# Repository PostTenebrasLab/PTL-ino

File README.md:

# PTL-ino

The PTL-ino (“petilino”) is a *uino-compatbile board that is fully made of easily solderable through-hole components.

You can find more general information at http://ptl-ino.com

The current Kicad file were made with Kicad 4.0.2, so please upgrade to Kicad 4 if you haven't already.
The Gerber file are there in case you simply want to order PCB directly to service like OSHPark or DirtyPCB.

If you plan to sell board based on this design, you have to remove our logo from the PCB.

PTL-ino board is licensed with Creative Common BY-SA 4.0 (https://creativecommons.org/licenses/by-sa/4.0/)

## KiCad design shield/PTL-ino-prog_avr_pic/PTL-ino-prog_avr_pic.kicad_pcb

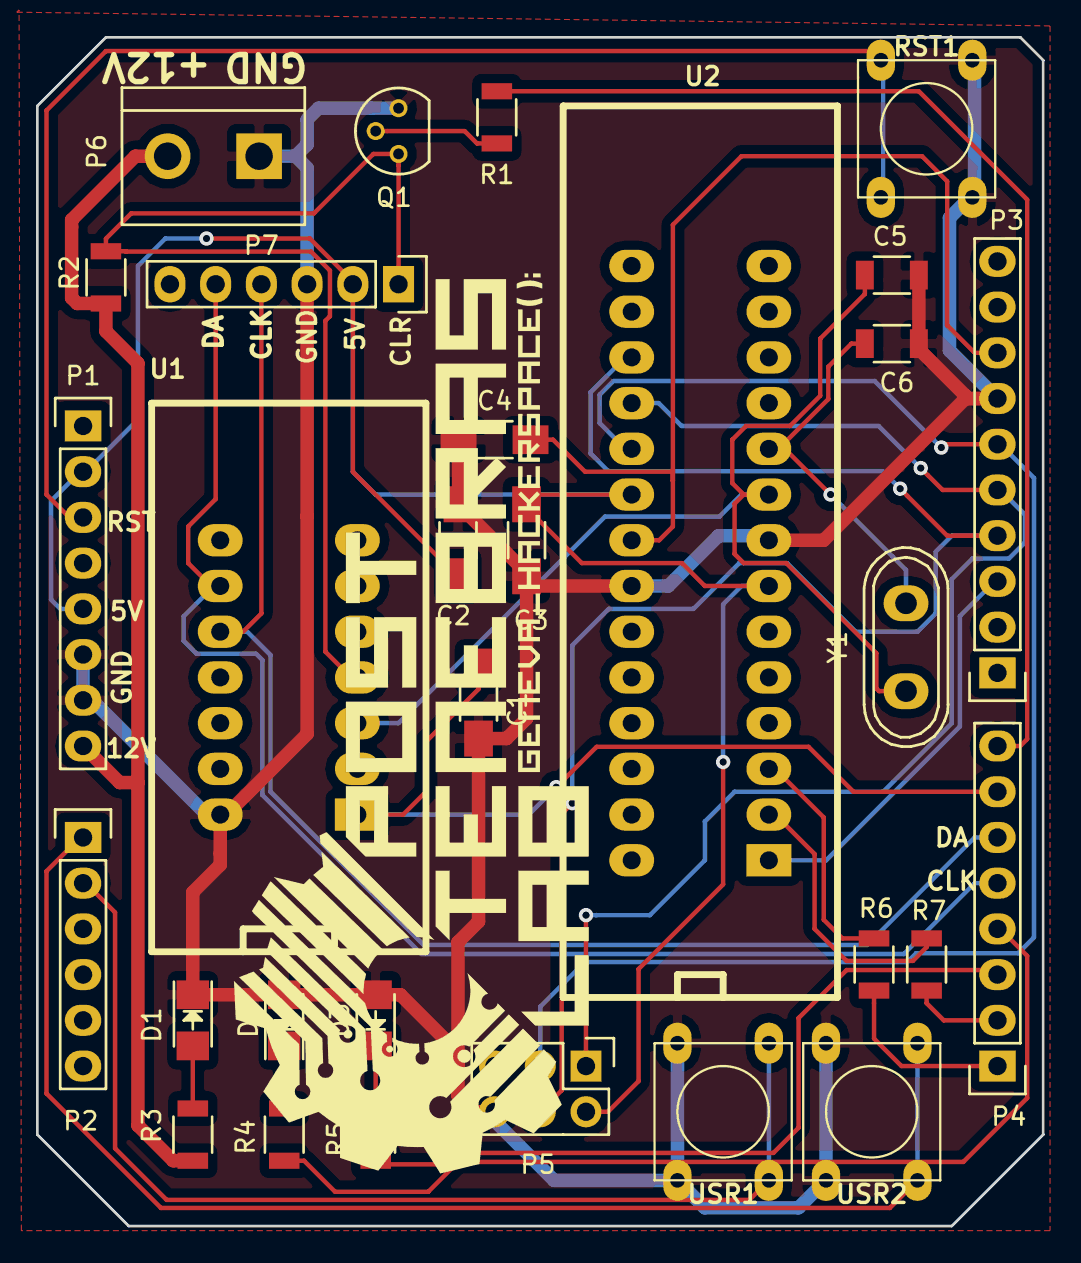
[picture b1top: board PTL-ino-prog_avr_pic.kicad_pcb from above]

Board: 2 copper layers, 55.9 x 66.0 mm, 30 parts (0 on the bottom side), 28 nets.

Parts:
C1: 220n; C_1206_HandSoldering
C2, C3, C4: 100n; C_1206_HandSoldering
C5, C6: 20pF; C_1206
D1: LED1; LED_1206
D2: LED2; LED_1206
D3: LED3; LED_1206
P1, P4: CONN_8; Pin_Header_Straight_1x08
P2, P7: CONN_6; Pin_Header_Straight_1x06
P3: CONN_10; Pin_Header_Straight_1x10
P5: CONN_3X2; Pin_Header_Straight_2x03
P6: CONN_01X02; bornier2
Q1: BC548; TO-92_Molded_Narrow
R1: 4K7; R_1206
R2: 10K; R_1206
R3: 1K; R_1206
R4, R5: 220; R_1206
R6, R7: R220; R_1206
RST1: RST; SW_PUSH_SMALL
U1: PIC16F1455; ZIF-14
U2: ATmega328; ZIF-28
USR1, USR2: SW_PUSH; SW_PUSH_SMALL
Y1: Crystal; Crystal_HC50-U_Vertical

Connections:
+5V: C2.1, C3.1, P1.2, P1.5, P5.2, P7.2, U2.7, U2.20
+12V: P1.8, P6.2, R2.1, R3.1
/0: P4.1, R6.1
/1: P4.2, R7.2
/2: P4.3, R5.2
/3: P4.4, R4.2
/4: P4.5, P7.5, U1.9
/5: P4.6, P7.4, U1.10
/6: C1.2, P4.7, U1.1
/7: P4.8, R1.2
/10: P3.3, U2.1
/11: P3.4, P5.4, U2.17
/12: P3.5, P5.1, U2.18
/13: P3.6, P5.3, U2.19
/14: P2.1, USR2.1
/15: P2.2, USR1.1
/AREF: C4.1, P3.8, U2.21
/~MCLR: P7.1, Q1.1, R2.2, U1.4
/~RST: P1.3, RST1.1
GND: C1.1, C2.2, C3.2, C4.2, C5.1, C6.2, D1.1, D2.2, D3.2, P1.6, P1.7, P3.7, P5.6, P6.1, P7.3, Q1.3, RST1.2, U1.14, U2.8, U2.22, USR1.2, USR2.2
unnamed: C5.2, U2.9, Y1.1
unnamed: C6.1, U2.10, Y1.2
unnamed: D1.2, R3.2
unnamed: D2.1, R4.1
unnamed: D3.1, R5.1
unnamed: Q1.2, R1.1
unnamed: R6.2, U2.3
unnamed: R7.1, U2.2

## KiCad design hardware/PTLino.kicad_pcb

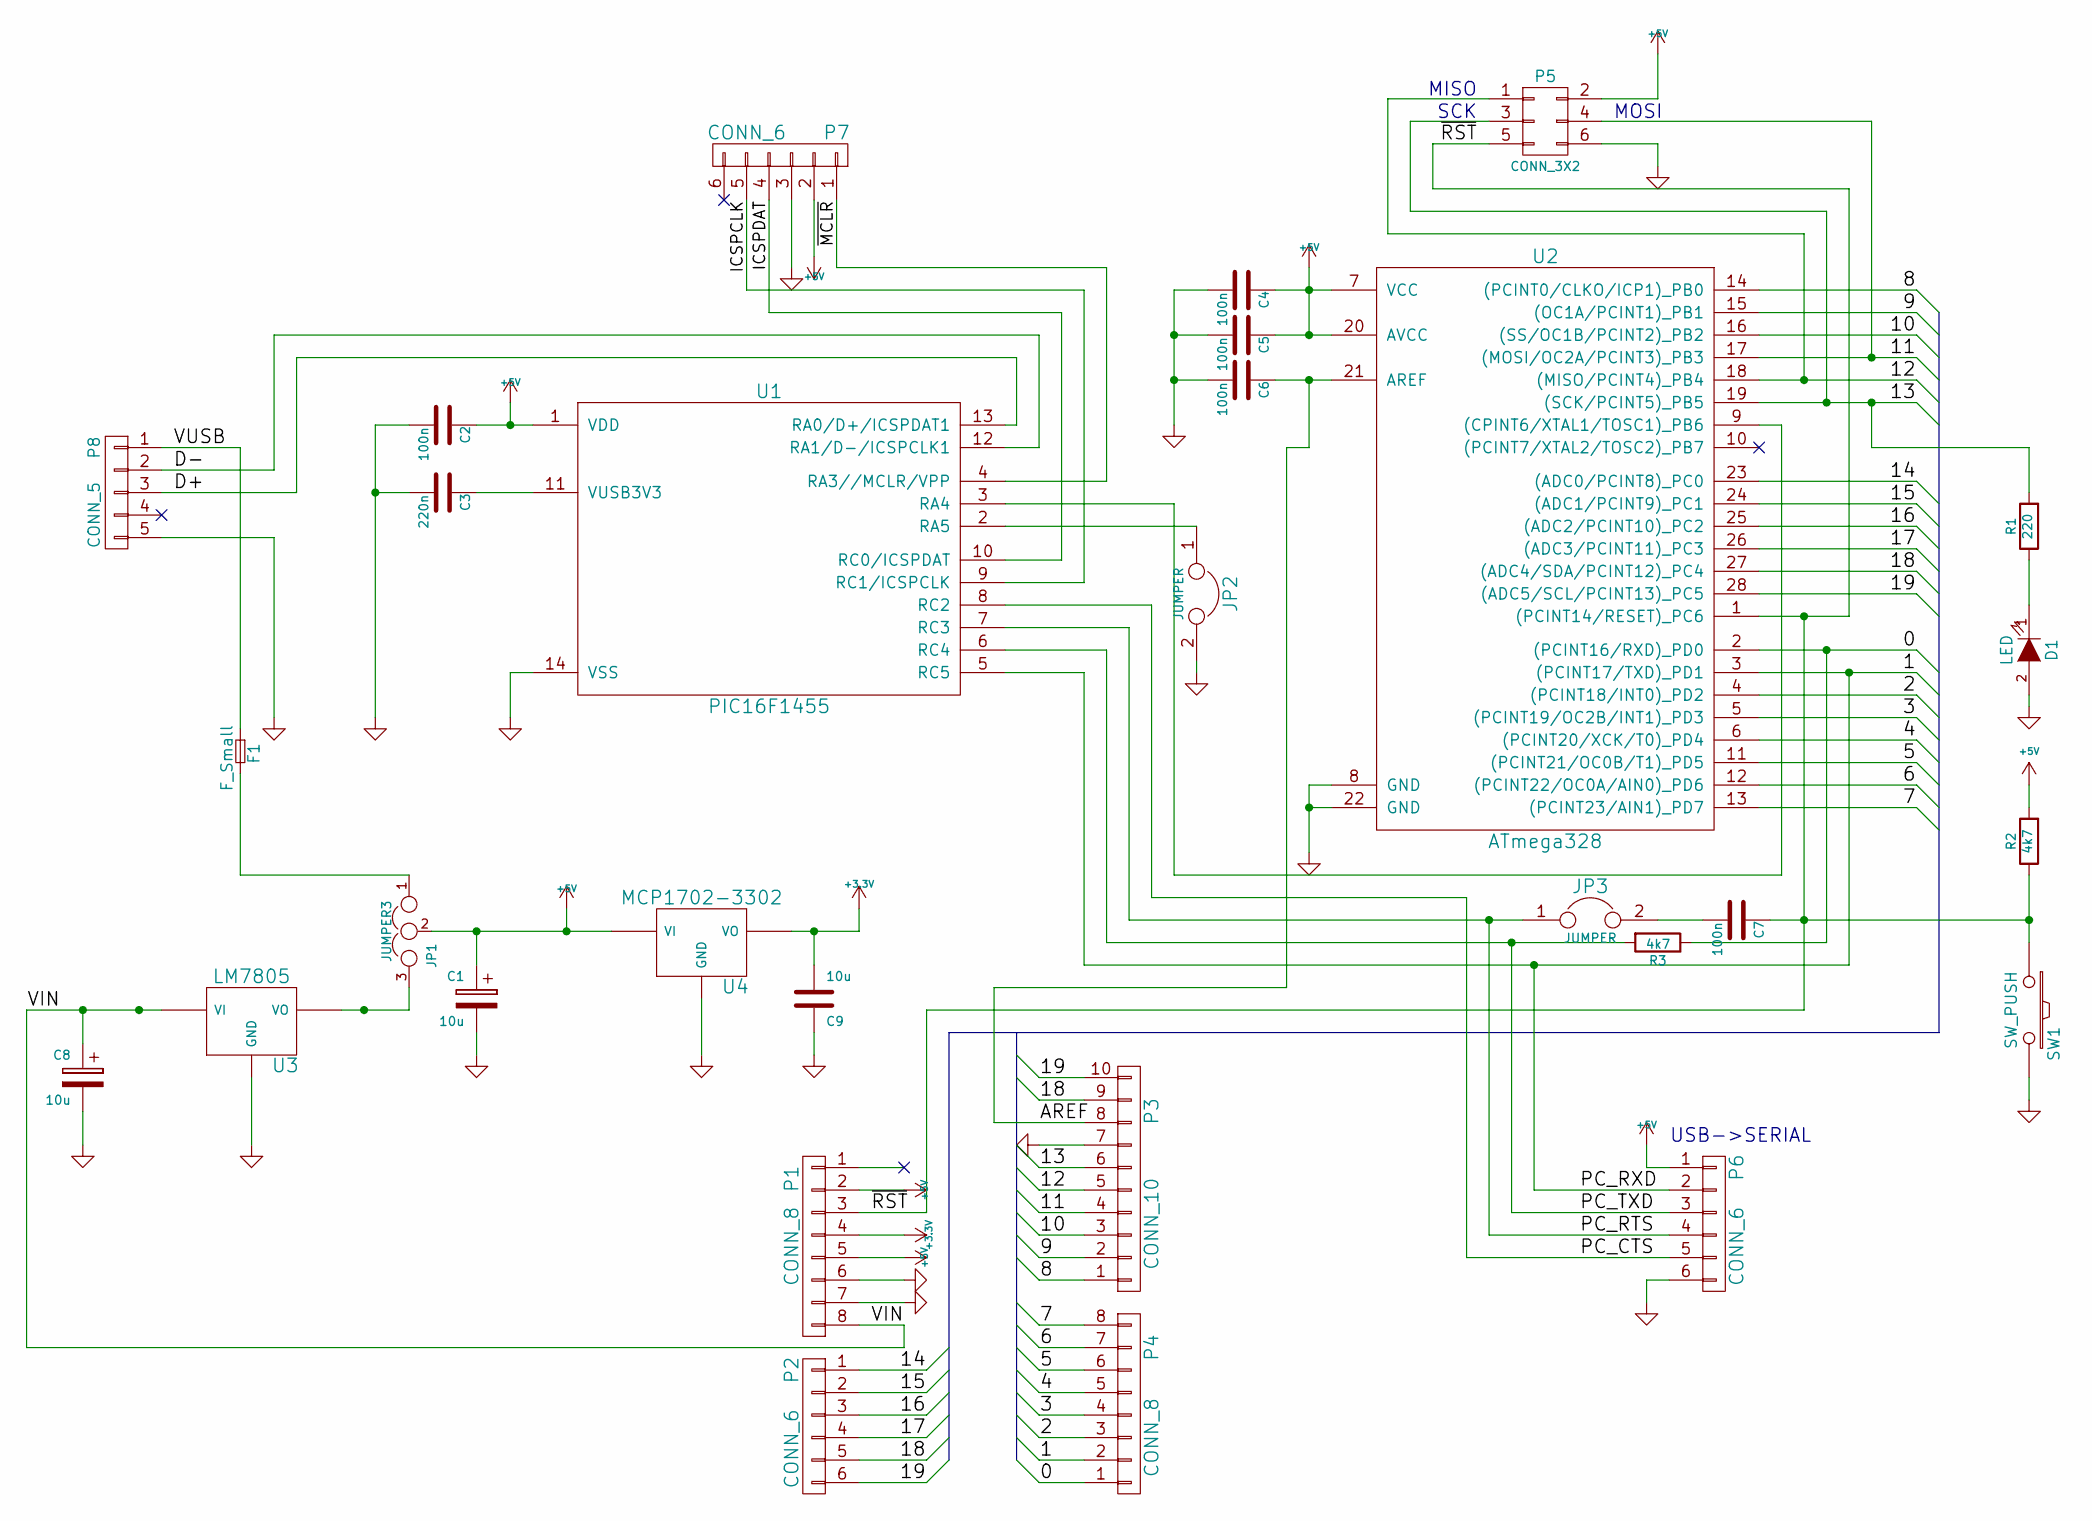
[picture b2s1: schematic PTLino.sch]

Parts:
C1, C8: 10u; C1V7H
C2, C4, C5, C6, C7: 100n; C1
C3: 220n; C1
C9: 10u; C1_pol
D1: LED; LEDV
F1: F_Small; F1
JP1: JUMPER3; solder-jumper-3
JP2, JP3: JUMPER; solder-jumper-2
P1, P4: CONN_8; SIL-8
P2, P6, P7: CONN_6; SIL-6
P3: CONN_10; SIL-10
P5: CONN_3X2; pin_array_3x2
P8: CONN_5; USB-mini-TH
R1: 220; R3-5
R2, R3: 4k7; R3-5
SW1: SW_PUSH; SW_PUSH_SMALL
U1: PIC16F1455; DIP-14__300_ELL
U2: ATmega328; DIP-28__300_ELL
U3: LM7805; TO220
U4: MCP1702-3302; TO92

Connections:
+3V3: C9.2, P1.4, U4.1 (VO)
+5V: C1.1, C2.1, C4.1, C5.1, JP1.2, P1.2, P1.5, P5.2, P6.1, P7.2, R2.2, U1.1 (VDD), U2.7 (VCC), U2.20 (AVCC), U4.2 (VI)
/0: P4.1, R3.1, U2.2 ((PCINT16/RXD)_PD0)
/1: P4.2, P6.2, U1.5 (RC5), U2.3 ((PCINT17/TXD)_PD1)
/2: P4.3, U2.4 ((PCINT18/INT0)_PD2)
/3: P4.4, U2.5 ((PCINT19/OC2B/INT1)_PD3)
/4: P4.5, U2.6 ((PCINT20/XCK/T0)_PD4)
/5: P4.6, U2.11 ((PCINT21/OC0B/T1)_PD5)
/6: P4.7, U2.12 ((PCINT22/OC0A/AIN0)_PD6)
/7: P4.8, U2.13 ((PCINT23/AIN1)_PD7)
/8: P3.1, U2.14 ((PCINT0/CLKO/ICP1)_PB0)
/9: P3.2, U2.15 ((OC1A/PCINT1)_PB1)
/10: P3.3, U2.16 ((SS/OC1B/PCINT2)_PB2)
/11: P3.4, P5.4, U2.17 ((MOSI/OC2A/PCINT3)_PB3)
/12: P3.5, P5.1, U2.18 ((MISO/PCINT4)_PB4)
/13: P3.6, P5.3, R1.2, U2.19 ((SCK/PCINT5)_PB5)
/14: P2.1, U2.23 ((ADC0/PCINT8)_PC0)
/15: P2.2, U2.24 ((ADC1/PCINT9)_PC1)
/16: P2.3, U2.25 ((ADC2/PCINT10)_PC2)
/17: P2.4, U2.26 ((ADC3/PCINT11)_PC3)
/18: P2.5, P3.9, U2.27 ((ADC4/SDA/PCINT12)_PC4)
/19: P2.6, P3.10, U2.28 ((ADC5/SCL/PCINT13)_PC5)
/AREF: C6.1, P3.8, U2.21 (AREF)
/D+: P8.3, U1.13 (RA0/D+/ICSPDAT1)
/D-: P8.2, U1.12 (RA1/D-/ICSPCLK1)
/ICSPCLK: P7.5, U1.9 (RC1/ICSPCLK)
/ICSPDAT: P7.4, U1.10 (RC0/ICSPDAT)
/PC_CTS: P6.5, U1.8 (RC2)
/PC_RTS: JP3.1, P6.4, U1.7 (RC3)
/PC_TXD: P6.3, R3.2, U1.6 (RC4)
/VIN: C8.1, P1.8, U3.2 (VI)
/VUSB: F1.1, P8.1
/~MCLR: P7.1, U1.4 (RA3//MCLR/VPP)
/~RST: C7.1, P1.3, P5.5, R2.1, SW1.1, U2.1 ((PCINT14/RESET)_PC6)
GND: C1.2, C2.2, C3.2, C4.2, C5.2, C6.2, C8.2, C9.1, D1.2 (A), JP2.2, P1.6, P1.7, P3.7, P5.6, P6.6, P7.3, P8.5, SW1.2, U1.14 (VSS), U2.8 (GND), U2.22 (GND), U3.3 (GND), U4.3 (GND)
unnamed: C3.1, U1.11 (VUSB3V3)
unnamed: C7.2, JP3.2
unnamed: D1.1 (K), R1.1
unnamed: F1.2, JP1.1
unnamed: JP1.3, U3.1 (VO)
unnamed: JP2.1, U1.2 (RA5)
unnamed: U1.3 (RA4), U2.9 ((CPINT6/XTAL1/TOSC1)_PB6)

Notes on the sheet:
MOSI
MISO
SCK
USB->SERIAL

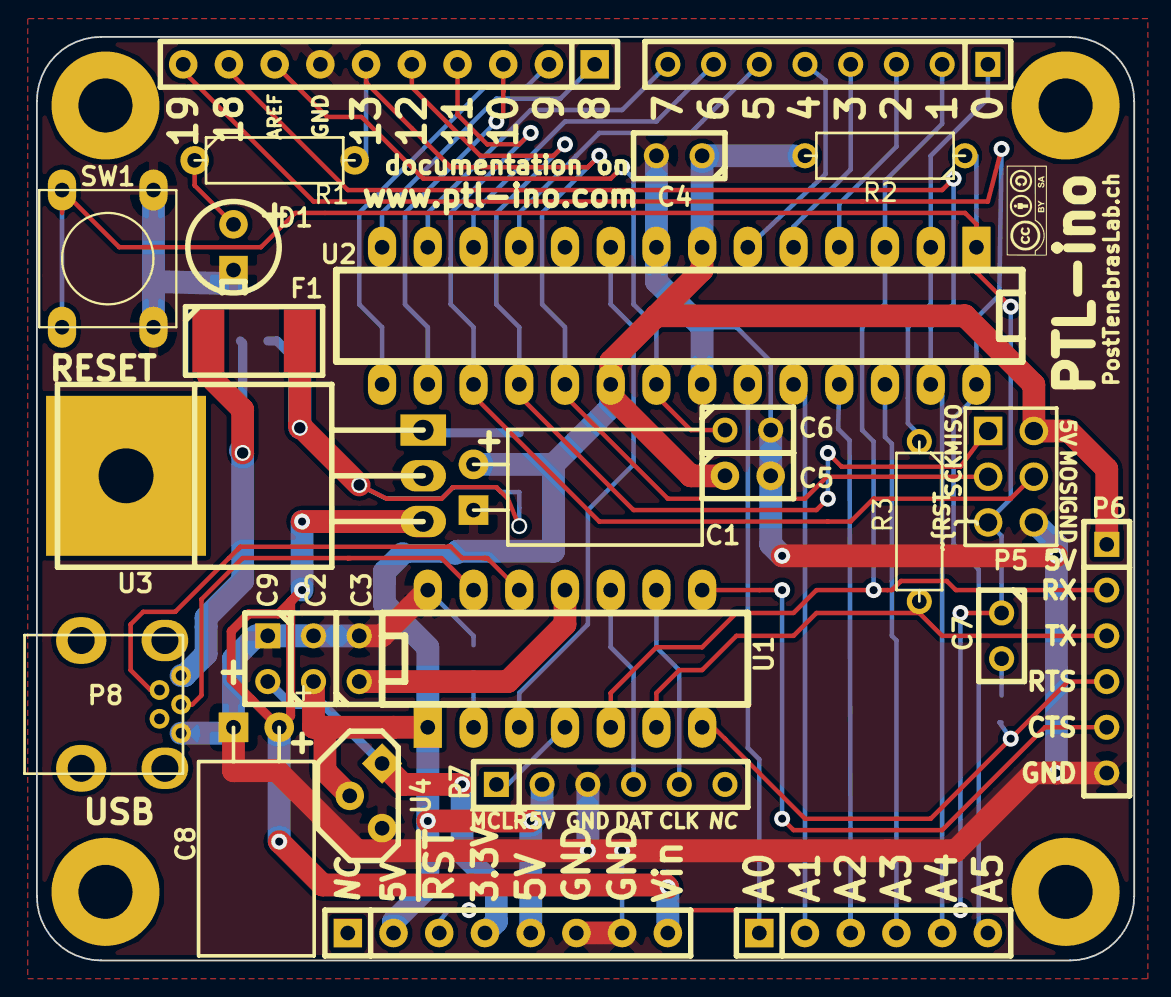
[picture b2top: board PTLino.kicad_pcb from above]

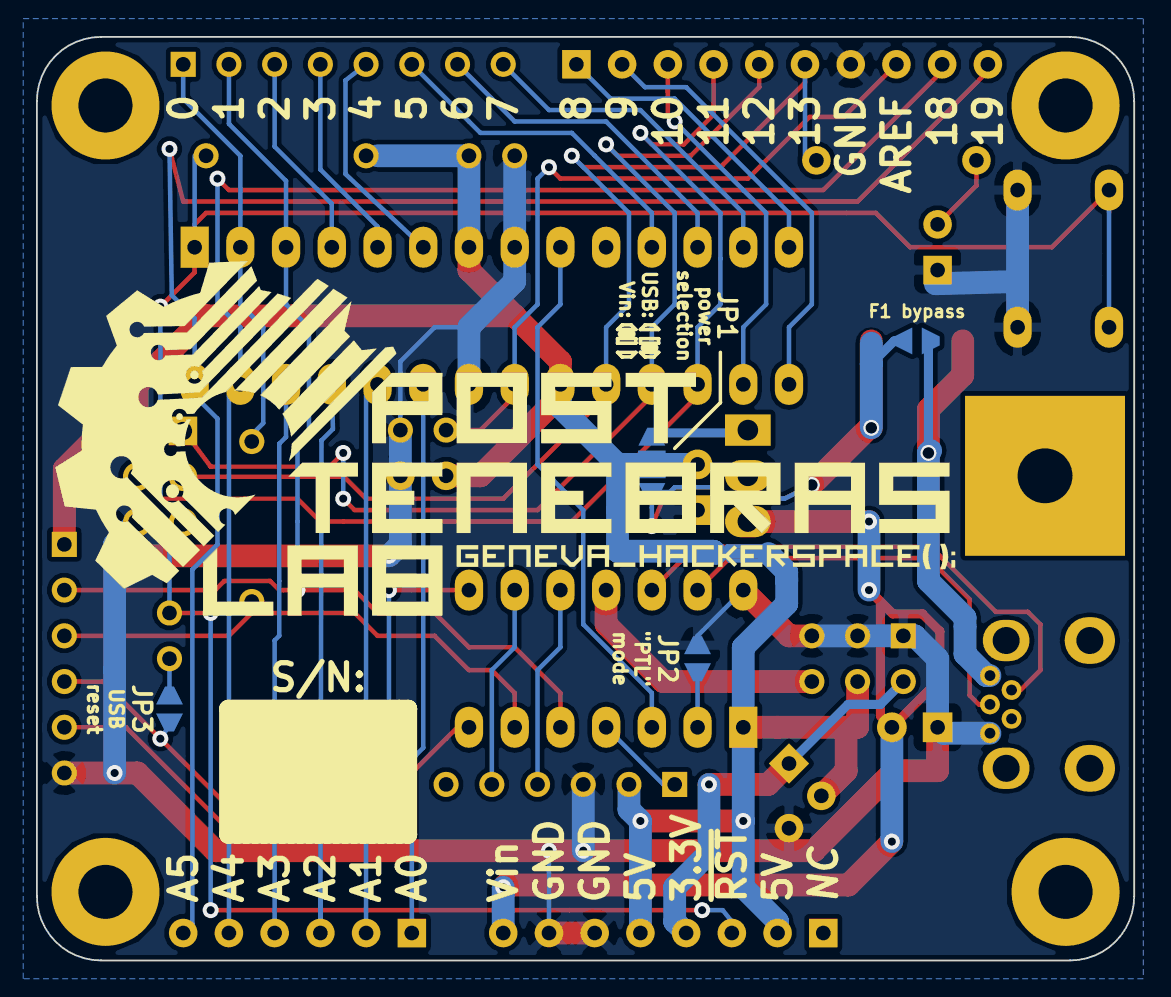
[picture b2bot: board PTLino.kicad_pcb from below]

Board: 2 copper layers, 61.0 x 51.3 mm, 35 parts (3 on the bottom side), 42 nets.

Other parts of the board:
CCBYSA: LOGO; Logo_silk_CC-BY-SA_5x2mm
mouting hole 3mm, mouting hole 3mm#2, mouting hole 3mm#3, mouting hole 3mm#4: VAL**; mounting-hole-3mm

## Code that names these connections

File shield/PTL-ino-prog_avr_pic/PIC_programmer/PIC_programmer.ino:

#define ICSPCLK 4
#define ICSPDAT 5
#define PICVDD  6
#define MCLR    7


#define CONFIG_WORD_1 0x0FA4
#define CONFIG_WORD_2 0x1FEF
#define WORD1_ADDR 7
#define WORD2_ADDR 7

enum pic_cmd {
  LOAD_CONF = 0,
  LOAD_FOR_PROG_MEM = 2,
  READ_FOR_PROG_MEM = 4,
  INC_ADDR = 6,
  RST_ADDR = 0x16,
  BEG_INTERNAL_TIMED_PROG = 0x8,
  BEG_EXTERNAL_TIMED_PROG = 0x18,
  BULK_ERASE_PROG_MEM = 0x9,
  ROW_ERASE_PROG_MEM = 0x11
};




/* Set vpp_entry_mode (programming mode)
 * 
 */
void vpp_entry_mode(){
  digitalWrite(ICSPCLK, LOW);
  digitalWrite(ICSPDAT, LOW);
  
  digitalWrite(MCLR, HIGH);
  delay(1);
  digitalWrite(PICVDD, HIGH);
  delay(1);
  
}

/* Write two word in config
 * 
 */
void set_pic_config(){

  // reset to 0x8000
  pic_cmd_call_wdata(LOAD_CONF, CONFIG_WORD_1);

  // jump to 0x8007
  for(int i = 0; i < WORD1_ADDR; i++)
    pic_cmd_call(INC_ADDR);

  pic_cmd_call(BEG_INTERNAL_TIMED_PROG);

  delayMicroseconds(2);
  
  // reset to 0x8000
  pic_cmd_call_wdata(LOAD_CONF, CONFIG_WORD_1);

  // jump to 0x8007
  for(int i = 0; i < WORD2_ADDR; i++)
    pic_cmd_call(INC_ADDR);

  pic_cmd_call(BEG_INTERNAL_TIMED_PROG);

  delayMicroseconds(2);

}

/* Write data from PIC's address 0x0000
 * 
 */
void write_data(short data_len, short * data){

  // Reset to address 0x000
  pic_cmd_call(RST_ADDR);

  // ERASE MEM
  pic_cmd_call(BULK_ERASE_PROG_MEM);
  // Max erase time 5ms
  delay(6);
  
  for(int i = 0; i < data_len; i++){

    // one word (16 bit word 0-14bit-0)
    for(int j = 0; j < 16; j++){
      digitalWrite(ICSPCLK, HIGH);
      digitalWrite(ICSPDAT, (((*data) >> j) & 1));
      digitalWrite(ICSPCLK, LOW);
    }
    
    data++;
    delayMicroseconds(2);
    pic_cmd_call(INC_ADDR);
    delayMicroseconds(2);
  }
}


/* Send cmd to pic with data as paylod (14 first bit significant)
 *  
 */
void pic_cmd_call_wdata(pic_cmd cmd, short data){

  //load configuration command
  digitalWrite(ICSPDAT, LOW);

  for( int i = 0; i < 6; i++){
    digitalWrite(ICSPCLK, HIGH);
    digitalWrite(ICSPDAT, ((cmd >> i) & 1));
    digitalWrite(ICSPCLK, LOW);
  }
  delayMicroseconds(2);  // one is enought

  // one word (14 bit word)
  for(int i = 0; i < 16; i++){
    digitalWrite(ICSPCLK, HIGH);
    digitalWrite(ICSPDAT, ((data >> i) & 1));
    digitalWrite(ICSPCLK, LOW);
  }
  
}

/* Send cmd to pic 
 *  
 */
void pic_cmd_call(pic_cmd cmd){

  //load configuration command
  digitalWrite(ICSPDAT, LOW);

  for( int i = 0; i < 6; i++){
    digitalWrite(ICSPCLK, HIGH);
    digitalWrite(ICSPDAT, ((cmd >> i) & 1));
    digitalWrite(ICSPCLK, LOW);
  }
  delayMicroseconds(2);  // one is enought
}


void setup() {
  // put your setup code here, to run once:

  pinMode(ICSPCLK, OUTPUT);
  pinMode(ICSPDAT, OUTPUT);
  pinMode(PICVDD, OUTPUT);
  pinMode(MCLR, OUTPUT);

  digitalWrite(ICSPCLK, LOW);
  digitalWrite(ICSPDAT, LOW);
  digitalWrite(PICVDD, LOW);
  digitalWrite(MCLR, LOW);

  // put in Vpp mode
  vpp_entry_mode();
  
  // set config
  set_pic_config();

  
}

void loop() {
  // put your main code here, to run repeatedly:

}

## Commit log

2015-11-14 Update README.md
    Initial simple readme with link to ptl-ino.com
2015-11-14 Created initial structure: Hardware and Software folders. Contain a .gitignore file as a workaround to empty dir.
2015-11-14 Added our doc on how to build the ptl-ino kit (FR + EN) This is a conversion of current doc to ASCIIDOC format. ptl.dozuki.com/Guide/How+to+build+a+PTL-ino+board/
2015-11-14 Corrected typo
2015-11-14 Small change to use the same typeset/syntax to refer to plus / minus sign
2015-11-14 Added simple makefile to generate doc (requires asciidoc)
2015-11-14 Removed useless .directory file for folder. Sorry
2015-11-16 Added fritzing design
2015-11-17 Added the windows "driver" (.inf file to indicate device is standard serial USB)
2016-03-27 updated to latest version of PTL-ino (v2) and added a template for doing PTL-ino shield.
2016-03-27 Added a few pictures, and clarified the use of our logo in case of commercial usage.
2016-03-28 Added meta dir to kicad shield template
2016-03-30 added default PIC firmware with quick Python tool to change serial number
2016-12-22 add new Atmeg, PIC programmer shield
2016-12-22 Added shield 3d pics
2016-12-30 added quartz
2016-12-30 Added PTL footprint
2016-12-31 Added new arduino sketch for PIC programmation
2017-01-20 Updated fritizing symbol for correct SVG export (see https://github.com/fritzing/fritzing-app/issues/1252 for details)
